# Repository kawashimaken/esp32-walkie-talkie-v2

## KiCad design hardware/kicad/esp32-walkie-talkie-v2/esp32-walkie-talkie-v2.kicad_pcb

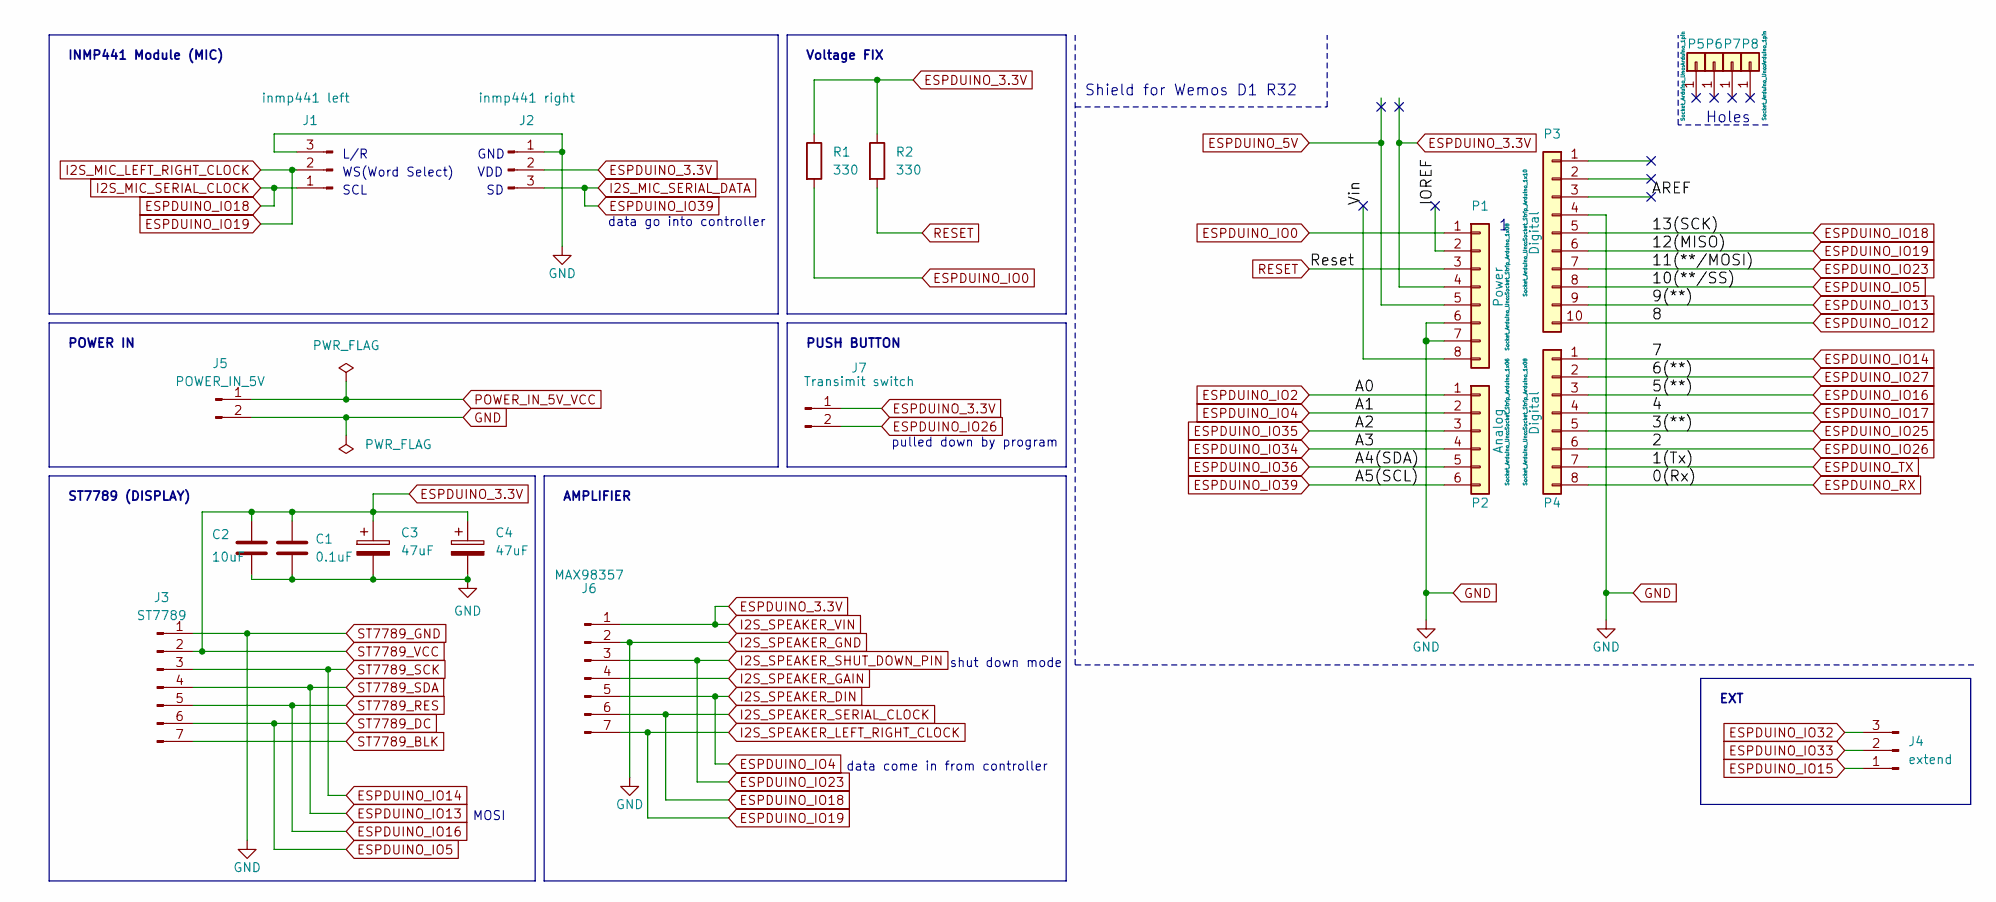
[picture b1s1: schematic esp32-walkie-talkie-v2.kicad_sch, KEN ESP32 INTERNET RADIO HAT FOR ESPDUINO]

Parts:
C1: 0.1uF; C_0603_1608Metric
C2: 10uF; CP_EIA-3528-12_Kemet-T
C3: 47uF; CP_Elec_6.3x5.8
C4: 47uF; C_Rect_L7.0mm_W2.0mm_P5.00mm
J1: inmp441 left; PinHeader_1x03_P2.54mm_Vertical
J2: inmp441 right; PinHeader_1x03_P2.54mm_Vertical
J3: ST7789; PinSocket_1x07_P2.54mm_Vertical
J4: extend; PinHeader_1x03_P2.54mm_Vertical
J5: POWER_IN_5V; PinHeader_1x02_P2.54mm_Vertical
J6: MAX98357; PinSocket_1x07_P2.54mm_Vertical
J7: Transimit switch; PinHeader_1x02_P2.54mm_Vertical
P1: Power; Socket_Strip_Arduino_1x08
P2: Analog; Socket_Strip_Arduino_1x06
P3: Digital; Socket_Strip_Arduino_1x10
P4: Digital; Socket_Strip_Arduino_1x08
P5, P6, P7, P8: CONN_01X01; Arduino_1pin
R1, R2: 330; R_1206_3216Metric

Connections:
/AREF: P3.3
/IOREF: P1.2
/Vin: P1.8
ESPDUINO_3.3V: C1.1, C2.1, C3.1, C4.1, J2.2, J3.2, J6.1, J7.1, P1.4, R1.1, R2.1
ESPDUINO_5V: P1.5
ESPDUINO_IO0: P1.1, R1.2
ESPDUINO_IO2: P2.1
ESPDUINO_IO4: J6.5, P2.2
ESPDUINO_IO5: J3.6, P3.8
ESPDUINO_IO12: P3.10
ESPDUINO_IO13: J3.4, P3.9
ESPDUINO_IO14: J3.3, P4.1
ESPDUINO_IO15: J4.1
ESPDUINO_IO16: J3.5, P4.3
ESPDUINO_IO17: P4.4
ESPDUINO_IO18: J1.1, J6.6, P3.5
ESPDUINO_IO19: J1.2, J6.7, P3.6
ESPDUINO_IO23: J6.3, P3.7
ESPDUINO_IO25: P4.5
ESPDUINO_IO26: J7.2, P4.6
ESPDUINO_IO27: P4.2
ESPDUINO_IO32: J4.3
ESPDUINO_IO33: J4.2
ESPDUINO_IO34: P2.4
ESPDUINO_IO35: P2.3
ESPDUINO_IO36: P2.5
ESPDUINO_IO39: J2.3, P2.6
ESPDUINO_RX: P4.8
ESPDUINO_TX: P4.7
GND: C1.2, C2.2, C3.2, C4.2, J1.3, J2.1, J3.1, J5.2, J6.2, P1.6, P1.7, P3.4
I2S_SPEAKER_GAIN: J6.4
POWER_IN_5V_VCC: J5.1
RESET: P1.3, R2.2
ST7789_BLK: J3.7

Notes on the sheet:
data go into controller
PUSH BUTTON
data come in from controller
ST7789 (DISPLAY)
EXT
L/R
pulled down by program
POWER IN
Holes
GND
Shield for Wemos D1 R32
AMPLIFIER
SCL
INMP441 Module (MIC)
Voltage FIX
MOSI
VDD
WS(Word Select)
shut down mode

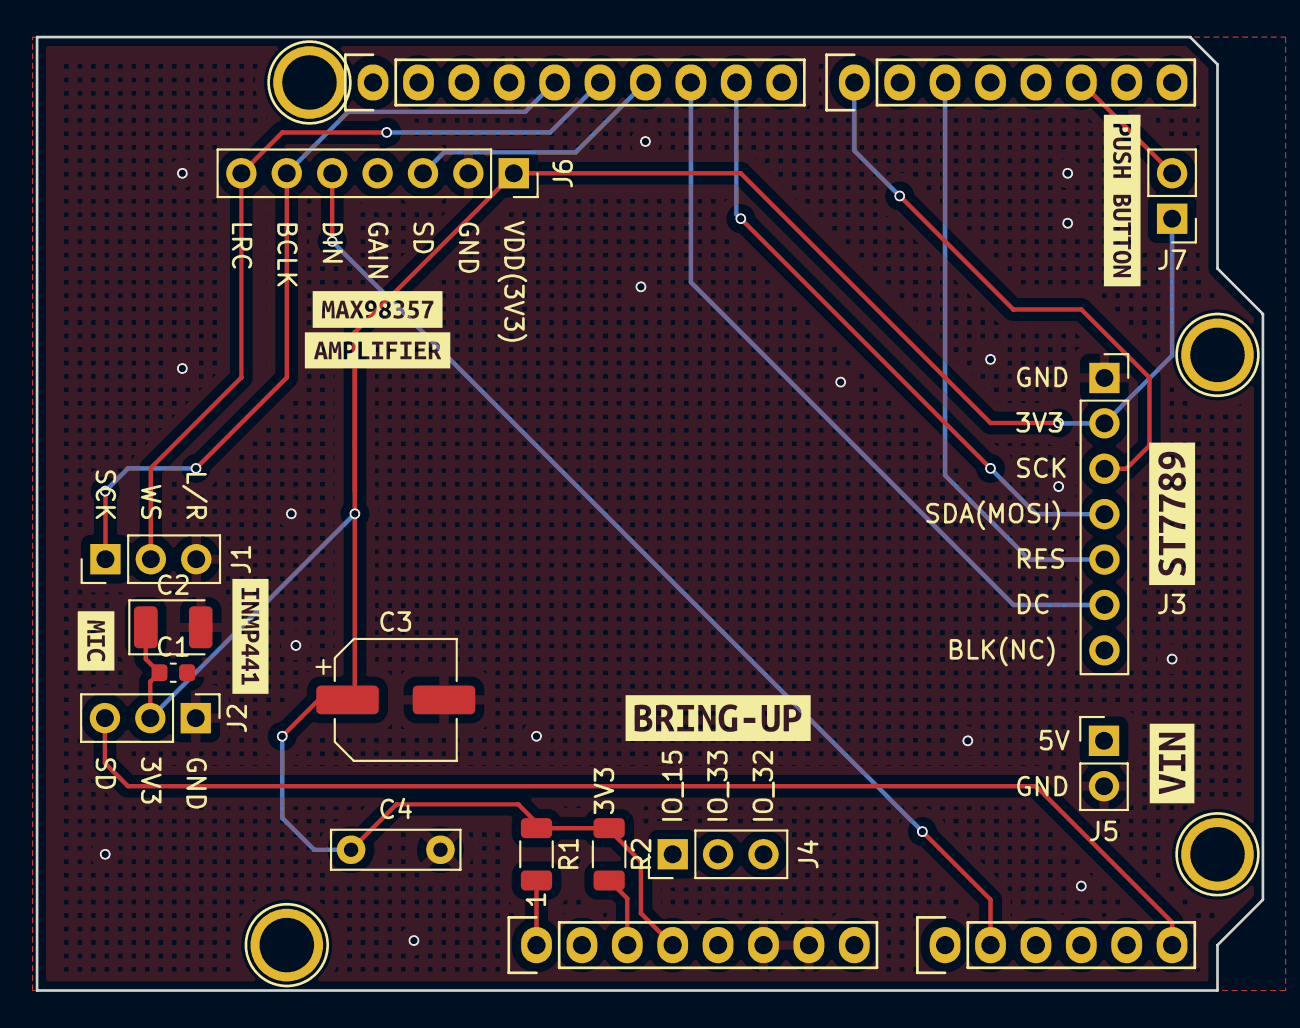
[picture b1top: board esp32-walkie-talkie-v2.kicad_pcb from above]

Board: 2 copper layers, 68.6 x 53.3 mm, 29 parts (0 on the bottom side), 14 nets.

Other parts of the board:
kibuzzard-62A4A2A0: G***; kibuzzard-62A4A2A0
kibuzzard-62A4A288: G***; kibuzzard-62A4A288
kibuzzard-62A534F6: G***; kibuzzard-62A534F6
kibuzzard-62A53545: G***; kibuzzard-62A53545
kibuzzard-62A53555: G***; kibuzzard-62A53555
kibuzzard-6279C31F: G***; kibuzzard-6279C31F
kibuzzard-6280E76A: G***; kibuzzard-6280E76A
kibuzzard-6280EDB6: G***; kibuzzard-6280EDB6

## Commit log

2022-06-11 add files
2022-06-11 remove old files
2022-06-12 update silk, export gerber
2022-06-12 add option capacitor
2022-06-12 add rect capacitor option
2022-06-12 add text, new copper fill
2022-06-21 send to pcbway
2022-06-21 add schematic pdf
2022-06-21 update svg and pdf
